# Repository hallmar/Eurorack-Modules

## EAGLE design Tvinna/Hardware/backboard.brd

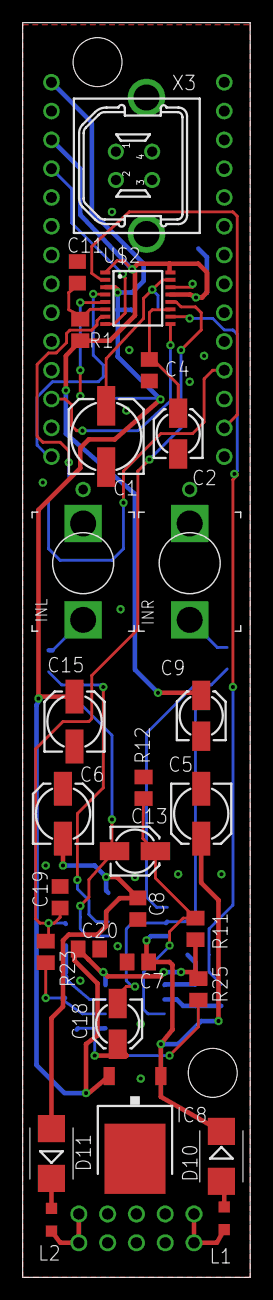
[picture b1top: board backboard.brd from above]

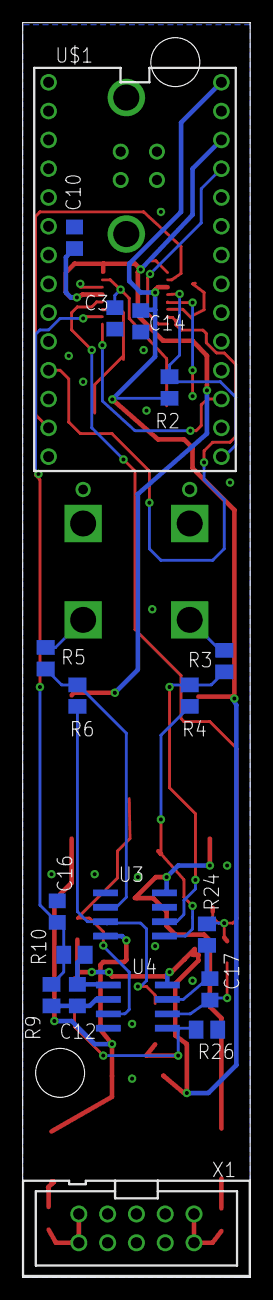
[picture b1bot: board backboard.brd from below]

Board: 2 copper layers, 20.1 x 110.7 mm, 47 parts (19 on the bottom side), 31 nets.

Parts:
C1: 100u; 153CLV-0605
C2, C9: 1u; 153CLV-0405
C3, C4, C7, C8, C10, C11, C14, C20: 100n; C0805
C5, C6, C15: 100µ; 153CLV-0505
C12, C17: 470p; C0805
C13, C18: 4.7u; 153CLV-0405
C16, C19: 2.7n; C0805
D10, D11: STPS1L30U; SMB
IC8: 7805DT; TO252
INL: THONKICONN16PJ138; WQP-PJ301M-12_JACK
INR: THONKICONN16PJ138; WQP-PJ301M-12_JACK
L1, L2: BLM21PG221SN1D; L2012C
R1: 5.1; M0805
R2: 10k; M0805
R3, R5, R11, R12, R25, R26: 100k; M0805
R4, R6: 47k; M0805
R9, R23: 634; M0805
R10, R24: 91; M0805
U3, U4: OP275; SO08
U$1: Teensy 3.2; TEENSY3.2_BAREBONES
U$2: CS5341; TSSOP16
X1: 2510-; PAK100/2500-10
X3: KUSBVX-BS1N

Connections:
3.3V: C9.+, C10.2, R1.1, U$1.3.3V, U$2.1, U$2.13, U$2.16
!RST: U$1.15/A1, U$2.9
+5V: C14.1, C15.+, C20.1, IC8.2, R2.2, R11.2, R25.2, U4.8, U$1.VIN, U$2.3
+12V: C5.+, C7.1, D10.C, IC8.1, U3.8
-12V: C6.-, C8.2, D11.A, U3.4
AINL: C16.2, R9.2, R10.2, U$2.10
AINR: C19.2, R23.2, R24.2, U$2.12
GND: C1.-, C2.-, C3.1, C4.2, C5.-, C6.+, C7.2, C8.1, C9.-, C10.1, C11.1, C14.2, C15.-, C16.1, C19.1, C20.2, IC8.3, INL.P$3_SLEEVE, INR.P$3_SLEEVE, R12.1, R26.1, U3.3, U3.5, U4.4, U$1.GND, U$2.5, U$2.14, X1.3, X1.4, X1.5, X1.6, X1.7, X1.8, X3.4, X3.M1, X3.M2
LRCLK: U$1.23/A9, U$2.8
MCLK: U$1.11, U$2.2
unnamed: C2.+, C4.1, U$2.11
unnamed: C1.+, C3.2, U$2.15
unnamed: C11.2, R1.2, U$2.6
unnamed: INR.P$1_TIP, R5.2
unnamed: INL.P$1_TIP, R3.2
unnamed: C13.-, R4.1, U3.1
unnamed: R3.1, R4.2, U3.2
unnamed: C18.-, R6.1, U3.7
unnamed: R5.1, R6.2, U3.6
unnamed: C13.+, R11.1, R12.2, U4.3
unnamed: C12.2, R9.1, U4.2
unnamed: C12.1, R10.1, U4.1
unnamed: C18.+, R25.1, R26.2, U4.5
unnamed: C17.2, R23.1, U4.6
unnamed: C17.1, R24.1, U4.7
unnamed: L1.1, X1.9, X1.10
unnamed: L2.1, X1.1, X1.2
unnamed: D10.A, L1.2
unnamed: D11.C, L2.2
SCLK/BCLK: U$1.9, U$2.7
SDATA: R2.1, U$1.13, U$2.4
